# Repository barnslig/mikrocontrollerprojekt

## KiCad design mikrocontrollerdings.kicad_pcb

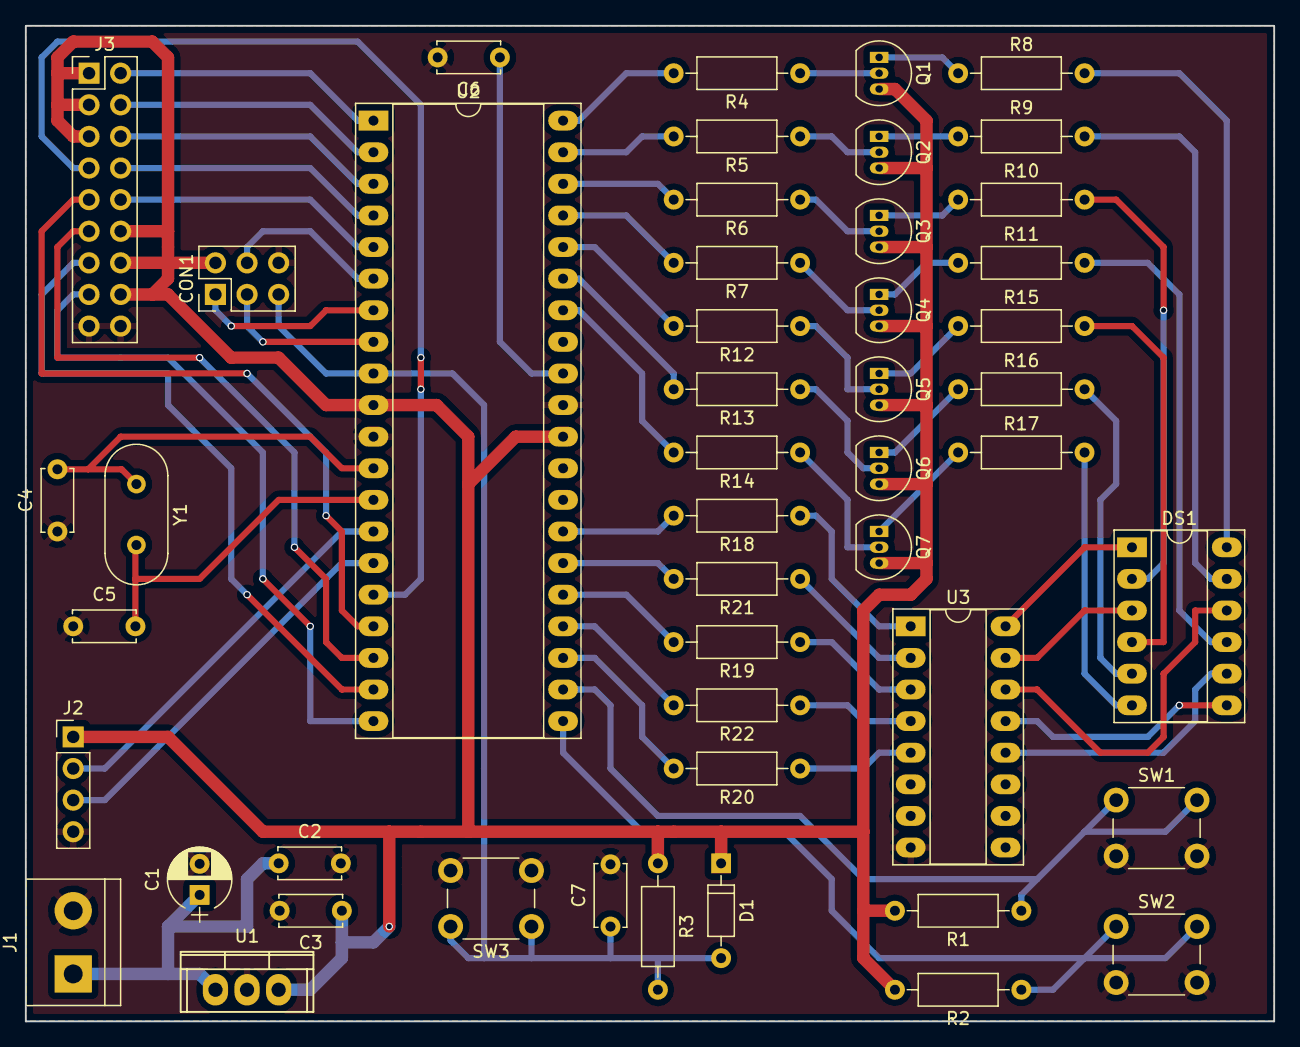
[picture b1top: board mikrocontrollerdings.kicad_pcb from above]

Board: 2 copper layers, 100.3 x 80.0 mm, 49 parts (0 on the bottom side), 67 nets.

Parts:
C1: 100µF; CP_Radial_D5.0mm_P2.50mm
C2: 0.33μF; C_Disc_D5.0mm_W2.5mm_P5.00mm
C3: 0.1μF; C_Disc_D5.0mm_W2.5mm_P5.00mm
C4, C5: 22pF; C_Disc_D5.0mm_W2.5mm_P5.00mm
C6: 100nF; C_Disc_D5.0mm_W2.5mm_P5.00mm
C7: 100 nF; C_Disc_D5.0mm_W2.5mm_P5.00mm
CON1: AVR-ISP-6; Pin_Header_Straight_2x03_Pitch2.54mm
D1: D1 1N4148; D_DO-35_SOD27_P7.62mm_Horizontal
DS1: TC07-11XWA; DIP-12_W7.62mm_Socket_LongPads
J1: Conn_Coaxial_Power; TerminalBlock_bornier-2_P5.08mm
J2: MAX232_CONN; Pin_Header_Straight_1x04_Pitch2.54mm
J3: EXT; Pin_Header_Straight_2x09_Pitch2.54mm
Q1, Q2, Q3, Q4, Q5, Q6, Q7: Q_PNP_CBE; TO-92_Inline_Narrow_Oval
R1, R2: 10K; R_Axial_DIN0207_L6.3mm_D2.5mm_P10.16mm_Horizontal
R3: 10k; R_Axial_DIN0207_L6.3mm_D2.5mm_P10.16mm_Horizontal
R4, R5, R6, R7, R12, R13, R14, R18, R19, R20, R21, R22: 0; R_Axial_DIN0207_L6.3mm_D2.5mm_P10.16mm_Horizontal
R8, R9, R10, R11, R15, R16, R17: 100; R_Axial_DIN0207_L6.3mm_D2.5mm_P10.16mm_Horizontal
SW1, SW2, SW3: SW_Push; SW_PUSH_6mm_h9.5mm
U1: LM7805; TO-220
U2: ATMEGA16A-PU; DIP-40_W15.24mm_Socket_LongPads
U3: ULN2003A; DIP-16_W7.62mm_Socket_LongPads
Y1: 14.7456Mhz; Crystal_HC18-U_Vertical

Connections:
+5V: C3.1, CON1.2, D1.1, J2.1, J3.1, J3.3, J3.5, J3.12, J3.14, J3.16, Q1.3, Q2.3, Q3.3, Q4.3, Q5.3, Q6.3, Q7.3, R1.2, R2.2, R3.1, U1.3, U2.10, U2.30
GND: C1.2, C2.2, C3.2, C4.1, C5.1, C6.2, C7.2, CON1.6, J1.2, J2.4, J3.17, J3.18, SW1.2, SW2.2, SW3.2, U1.2, U2.11, U2.31, U3.8
MISO: CON1.1, U2.7
MOSI: CON1.4, U2.6
unnamed: C6.1, U2.32
unnamed: DS1.1, U3.16
unnamed: DS1.3, U3.15
unnamed: DS1.7, U3.13
unnamed: DS1.8, U3.12
unnamed: DS1.10, U3.14
unnamed: Q1.1, R8.1
unnamed: Q1.2, R4.1
unnamed: Q2.1, R9.1
unnamed: Q2.2, R5.1
unnamed: Q3.1, R10.1
unnamed: Q3.2, R6.1
unnamed: Q4.1, R11.1
unnamed: Q4.2, R7.1
unnamed: Q5.1, R15.1
unnamed: Q5.2, R12.1
unnamed: Q6.1, R16.1
unnamed: Q6.2, R13.1
unnamed: Q7.1, R17.1
unnamed: Q7.2, R14.1
unnamed: R18.1, U3.1
unnamed: R19.1, U3.3
unnamed: R20.1, U3.5
unnamed: R21.1, U3.2
unnamed: R22.1, U3.4
PA0: R4.2, U2.40
PA1: R5.2, U2.39
PA2: R6.2, U2.38
PA3: R7.2, U2.37
PA4: R12.2, U2.36
PA5: R13.2, U2.35
PA6: R14.2, U2.34
PB0: J3.2, U2.1
PB1: J3.4, U2.2
PB2: J3.6, U2.3
PB3: J3.8, U2.4
PB4: J3.10, U2.5
PC0: R1.1, SW1.1, U2.22
PC1: R20.2, U2.23
PC2: R22.2, U2.24
PC3: R19.2, U2.25
PC4: R21.2, U2.26
PC5: R18.2, U2.27
PD2: J3.7, U2.16
PD3: J3.9, U2.17
PD4: J3.11, U2.18
PD5: J3.13, U2.19
PD6: J3.15, U2.20
PD7: R2.1, SW2.1, U2.21
R1: DS1.12, R8.2
R2: DS1.11, R9.2
R3: DS1.2, R10.2
R4: DS1.9, R11.2
R5: DS1.4, R15.2
R6: DS1.5, R16.2
R7: DS1.6, R17.2
RST: C7.1, CON1.5, D1.2, R3.2, SW3.1, U2.9
RXD: J2.2, U2.14
SCK: CON1.3, U2.8
TXD: J2.3, U2.15
VCC: C1.1, C2.1, J1.1, U1.1
XTAL1: C5.2, U2.13, Y1.2
XTAL2: C4.2, U2.12, Y1.1

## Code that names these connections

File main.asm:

.include "m16Adef.inc"

; gavrasm main.asm
; avrdude -p m16 -c usbasp -U main.hex

.equ DEBOUNCE_COUNT = 20

; uart configuration. see datasheet page 147
.equ F_CPU = 4000000
.equ BAUD  = 9600
.equ MYUBRR = F_CPU/16/BAUD-1

; register names
.def temp = r16
.def btn_debounce_counter = r17
.def current_row = r27
.def current_row_bit = r28
.def current_number = r29

.org 0x00
	rjmp main

.org INT0addr
	rjmp up_button

.org INT1addr
	rjmp down_button

.org OVF2addr
	rjmp update_button_debounce

.org OVF0addr
	rjmp update_display

.org URXCaddr
	rjmp receive_value

patterns:
	; 0
	.db 0b00011100, 0b00100010, 0b00100010, 0b00100010, 0b00100010, 0b00100010, 0b00011100, 0
	; 1
	.db 0b00000110, 0b00011010, 0b00110010, 0b00000010, 0b00000010, 0b00000010, 0b00000010, 0
	; 2
	.db 0b00011100, 0b00100010, 0b00000010, 0b00000100, 0b00001000, 0b00010000, 0b00111110, 0
	; 3
	.db 0b00111110, 0b00000010, 0b00000010, 0b00111110, 0b00000010, 0b00000010, 0b00111110, 0
	; 4
	.db 0b00100010, 0b00100010, 0b00100010, 0b00111110, 0b00000010, 0b00000010, 0b00000010, 0
	; 5
	.db 0b00111110, 0b00100000, 0b00100000, 0b00111100, 0b00000010, 0b00000010, 0b00111100, 0
	; 6
	.db 0b00011110, 0b00100000, 0b00100000, 0b00111100, 0b00100010, 0b00100010, 0b00011100, 0
	; 7
	.db 0b00111110, 0b00000010, 0b00000100, 0b00011100, 0b00010000, 0b00100000, 0b00100000, 0
	; 8
	.db 0b00011100, 0b00100010, 0b00100010, 0b00011100, 0b00100010, 0b00100010, 0b00011100, 0
	; 9
	.db 0b00011100, 0b00100010, 0b00100010, 0b00011110, 0b00000010, 0b00000010, 0b00111100, 0
	; A
	.db 0b00011100, 0b00100010, 0b00100010, 0b00111110, 0b00100010, 0b00100010, 0b00100010, 0
	; B
	.db 0b00111100, 0b00100010, 0b00100010, 0b00111100, 0b00100010, 0b00100010, 0b00111100, 0
	; C
	.db 0b00011110, 0b00100000, 0b00100000, 0b00100000, 0b00100000, 0b00100000, 0b00011110, 0
	; D
	.db 0b00111100, 0b00100010, 0b00100010, 0b00100010, 0b00100010, 0b00100010, 0b00111100, 0
	; E
	.db 0b00111110, 0b00100000, 0b00100000, 0b00111110, 0b00100000, 0b00100000, 0b00111110, 0
	; F
	.db 0b00111110, 0b00100000, 0b00100000, 0b00111110, 0b00100000, 0b00100000, 0b00100000, 0

main:
	; enable stack pointer
	ldi temp, high(RAMEND)
	out SPH, temp
	ldi temp, low(RAMEND)
	out SPL, temp

	; PA0-PA6: rows
	ldi temp, 0b01111111
	out DDRA, temp

	; PC1-PC5: cols
	ldi temp, 0b00111110
	out DDRC, temp

	; create 8 bit timer counter for button debouncing. prescaler is clock/1024 --> ~4kHz
	ldi temp, (1 << CS20) | (1 << CS22)
	out TCCR2, temp

	; create 8 bit timer counter for the display. prescaler is clock/8 --> 500kHz
	ldi temp, (1 << CS01)
	out TCCR0, temp

	; enable interrupts when the timer counters overflow
	; display interval: 500kHz/256 --> ~2kHz --> 200ms
	; button debouncer interval: 4kHz/256 --> ~15Hz --> 66ms
	ldi temp, (1 << TOIE0) | (1 << TOIE2)
	out TIMSK, temp

	; INT0 und INT1 auf steigende Flanke konfigurieren
	ldi temp, (1 << ISC01) | (1 << ISC11)
	out MCUCR, temp

	; INT0 und INT1 aktivieren
	ldi temp, (1 << INT0) | (1 << INT1)
	out GICR, temp

	; set uart baudrate
	ldi temp, HIGH(MYUBRR)
	out UBRRH, temp
	ldi temp, LOW(MYUBRR)
	out UBRRL, temp

	; set uart frame format: 8data, 2stop bit
	ldi temp, (1 << URSEL) | (1 << USBS) | (3 << UCSZ0)
	out UCSRC, temp

	; enable uart receive and transmit
	ldi temp, (1 << RXEN) | (1 << TXEN)
	out UCSRB, temp

	; enable uart receive interrupt
	sbi UCSRB, RXCIE

	; pattern buffer (port order is a bit messed up ;-)))
	ldi r20, 0b00100000
	ldi r26, 0b00010000
	ldi r25, 0b00001000
	ldi r24, 0b00000100
	ldi r23, 0b00000010
	ldi r22, 0b00110000
	ldi r21, 0b00001100

	; current row number
	ldi current_row, 0

	; current row bits
	ldi current_row_bit, 0b10000000

	; current input number
	ldi current_number, 0

	; button debounce counter
	ldi btn_debounce_counter, 0

	; enable interrupts
	sei

loop:
	rjmp loop

do_nothing:
	reti

display_input_number:
	rcall transmit_input_number

	; calculate pattern address
	ldi ZH, HIGH(patterns*2)
	ldi ZL, LOW(patterns*2)

	ldi temp, 8
	mul temp, current_number
	add ZL, r0

	lpm r20, Z+
	lpm r26, Z+
	lpm r25, Z+
	lpm r24, Z+
	lpm r23, Z+
	lpm r22, Z+
	lpm r21, Z+

	ret

;;;;;;;;;;;;;;;;
; UART HANDLER ;
;;;;;;;;;;;;;;;;

transmit_input_number:
	cpi current_number, 10
	brge transmit_input_character

	ldi temp, 48
	add temp, current_number
	out UDR, temp

	ret

transmit_input_character:
	ldi temp, 55
	add temp, current_number
	out UDR, temp

	ret

receive_value:
	in temp, UDR

	; ASCII 48-57: 0-9
	; ASCII 65-70: A-F
	cpi temp, 48
	brlt do_nothing
	cpi temp, 71
	brge do_nothing
	cpi temp, 58
	brlt receive_value_number
	cpi temp, 65
	brlt do_nothing

	subi temp, 55
	mov current_number, temp

	rcall display_input_number

	reti

receive_value_number:
	subi temp, 48
	mov current_number, temp

	rcall display_input_number

	reti

;;;;;;;;;;;;;;;;;;
; BUTTON HANDLER ;
;;;;;;;;;;;;;;;;;;

update_button_debounce:
	cpi btn_debounce_counter, 0
	breq do_nothing

	dec btn_debounce_counter
	reti

up_button:
	; do nothing if button debounce counter is not zero
	cpi btn_debounce_counter, 0
	brne do_nothing

	; do nothing if upper bound is reached
	cpi current_number, 15
	brge do_nothing

	; increment input number
	inc current_number

	; set button debounce counter
	ldi btn_debounce_counter, DEBOUNCE_COUNT

	rcall display_input_number

	reti

down_button:
	; do nothing if button debounce counter is not zero
	cpi btn_debounce_counter, 0
	brne do_nothing

	; do nothing if lower bound is reached
	cpi current_number, 0
	breq do_nothing

	; decrement input number
	dec current_number

	; set button debounce counter
	ldi btn_debounce_counter, DEBOUNCE_COUNT

	rcall display_input_number

	reti

;;;;;;;;;;;;;;;;;;;;;;;;
; DISPLAY MULTIPLEXING ;
;;;;;;;;;;;;;;;;;;;;;;;;

update_display:
	; turn off row that we want to enable
	mov temp, current_row_bit
	com temp
	out PORTA, temp

	cpi current_row, 0
	breq row_0
	cpi current_row, 1
	breq row_1
	cpi current_row, 2
	breq row_2
	cpi current_row, 3
	breq row_3
	cpi current_row, 4
	breq row_4
	cpi current_row, 5
	breq row_5
	cpi current_row, 6
	breq row_6

row_0:
	out PORTC, r20
	rjmp continue_update_display
row_1:
	out PORTC, r21
	rjmp continue_update_display
row_2:
	out PORTC, r22
	rjmp continue_update_display
row_3:
	out PORTC, r23
	rjmp continue_update_display
row_4:
	out PORTC, r24
	rjmp continue_update_display
row_5:
	out PORTC, r25
	rjmp continue_update_display
row_6:
	out PORTC, r26
	rjmp continue_update_display

continue_update_display:
	; increment current row when it is less than 7
	cpi current_row, 7
	brlt next_row

	; reset
	ldi current_row, 0
	ldi current_row_bit, 0b10000000

	reti

next_row:
	inc current_row
	lsr current_row_bit

	reti

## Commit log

2017-11-09 Kondensator zwischen AREF und GND hinzugefügt
    Das Datenblatt sagt, man soll einen Kondensator einbauen. In Foren
    schreiben Leute, dass 100nF eine gute Idee sind. Hab ich mal übernommen.
2017-11-09 Added Reset
2017-11-09 Add power conn, add increment/decrement button
2017-11-09 annotate components
2017-11-09 lazy add new led matrix
2017-11-13 Add MAX232 and EXT connectors, add additional resistors to LED inputs
2017-11-13 change to PNP transistors for load switching
2017-11-23 add resistors to uln2003a
2017-11-23 add netlist
2017-11-23 first pcb draft with some unconnected ground plane isles
2017-11-30 Finish PCB
    + Add GND plane to backside to fix unconnected ground pins
    + Resize +5V track to 1mm
    + Rename LED matrix to correct part
2018-01-29 yay our program
2018-01-29 implement button debouncing
2018-01-29 Implement serial connection, fix pattern data storage
2018-01-29 give registers names
